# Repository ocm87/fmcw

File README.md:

# ELEC4907 FMCW/Dopper Radar Capstone Project
Year: 2024-2025

Supervisor: Shulabh Gupta

Team Members: Carter Livermore, Jin Her, Max Hecht, Owen MacIntosh

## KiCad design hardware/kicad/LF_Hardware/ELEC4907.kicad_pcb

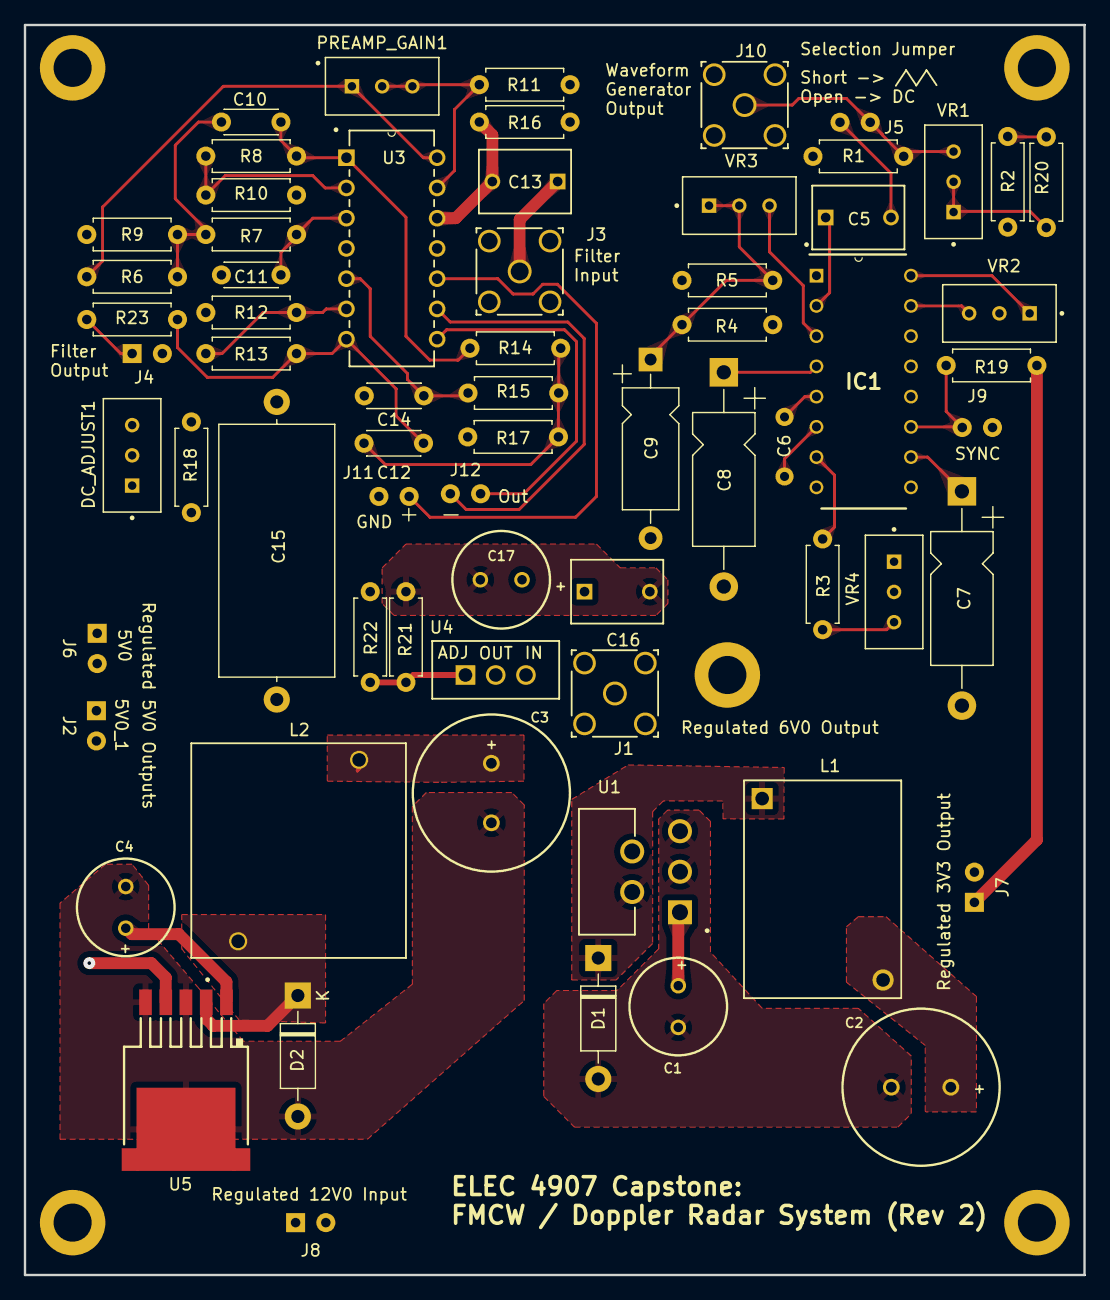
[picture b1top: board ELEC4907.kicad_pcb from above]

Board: 4 copper layers, 89.0 x 105.0 mm, 71 parts (0 on the bottom side), 40 nets.

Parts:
C1, C4, C17: 100uF; 100uF_RadialCap
C2, C3: 330uF; 330uF_radialCap
C5, C13, C16: 1uF; R82-D_KEM
C6: 0.47uF; 0.47uF_cap
C7, C8: 1uF; AxialCap_P18
C9: 10uF; Cap_P15
C10, C11, C12: 100pF; Disc_Cap_P5mm
C14: 150pF; Disc_Cap_P5mm
C15: 10uF; Axial_Cap_P25
D1, D2: 1N5819; D_DO-41_SOD81_P10.16mm_Horizontal
DC_ADJUST1: 100k; TRIM_3296W-1-503LF
GND: MountingHole_3.2mm_M3_ISO14580_Pad
GND#2, GND#3, GND#4: MountingHole_3.2mm_M3_ISO14580_Pad
IC1: XR2206CP-F; DIP794W56P254L2013H533Q16N
J1, J3, J10: RF2-04A-T-00-50-G; CONN_RF2-04A-T-00-50-G_ADM
J2, J4, J5, J6, J7, J8, J9, J11, J12: 2-54mm_Spacing
L1: IND_PE-526xx_V_PUL
L2: 330uH Inductor
PREAMP_GAIN1: 100k; TRIM_3296W-1-503LF
R1, R7: 100k; resistor
R2: 39k; resistor
R3: 33k; resistor
R4, R5: 4.7k; resistor
R6, R14: 82k; resistor
R8, R10, R12, R13: 27k; resistor
R9, R17: 1M; resistor
R11: 220; resistor
R15: 43k; resistor
R16, R19: 10k; resistor
R18: 5.6k; resistor
R20: 560k; resistor
R21: 1.5k; resistor
R22: 390; resistor
R23: 0; resistor
U1: LM2575T-3.3; (3v3)TO170P470X1016X2092-5P
U3: LT1214CN-PBF; PDIP-14_N_LIT
U4: LM317T; TO-220_STM
U5: LM2575S-5.0/NOPB; KTT0005B
VR1: 100k; TRIM_3296W-1-503LF
VR2, VR4: 25k; TRIM_3296W-1-503LF
VR3: 50k; TRIM_3296W-1-503LF

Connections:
/Filter/PRE_OUT: PREAMP_GAIN1.1, R6.1, U3.14 (OUT_D)
/Filter/STAGE1_OUT: C10.1, R8.2, R14.1, U3.1 (OUT_A)
/Filter/VREF: C11.1, C14.1, C15.1, DC_ADJUST1.2, DC_ADJUST1.3, R9.1, R10.1, R11.2, R12.1, R16.2, R17.1, R18.1
/Filter/Vcc: C1.1, C4.1, C8.1, C16.1, DC_ADJUST1.1, IC1.4 (VCC), J8.1, R4.1, U1.1 (VIN), U3.4 (V+), U4.3 (INPUT), U5.1 (VIN)
/Filter/VinLPF: C13.1, J3.1
/Filter/VoutLPF: C12.1, R13.2, R23.1, U3.7 (OUT_B)
/Power_Regulation/3V3: C2.1, J7.2, L1.2, R19.2, U1.4 (FB)
/Power_Regulation/3V3_UNREG: D1.1 (K), L1.1, U1.2 (OUTPUT)
/Power_Regulation/5V0: C3.1, J2.1, J6.2, L2.1, U5.4 (FB)
/Power_Regulation/5V0_UNREG: D2.1 (K), L2.2, U5.2 (OUT)
/Power_Regulation/6V0: C17.1, J1.1, R1.1, R22.2, U4.2 (OUTPUT)
/Waveform_Generator/Triangular_Waveform: J5.2, J10.1, R1.2, VR1.3
GND: C1.2, C2.2, C3.2, C4.2, C7.2, C8.2, C9.2, C15.2, C16.2, C17.2, D1.2 (A), D2.2 (A), GND.1, GND#2.1, GND#3.1, GND#4.1, IC1.1 (AMSI), IC1.12 (GND), J1.2 (GND), J1.3, J1.4, J1.5, J2.2, J3.2 (GND), J3.3, J3.4, J3.5, J4.1, J6.1, J7.1, J8.2, J9.2, J10.2 (GND), J10.3, J10.4, J10.5, J11.2, R2.2, R5.2, R18.2, R21.2, U1.3 (GND), U1.5 (ON/OFF), U3.11 (V-), U5.3 (GND), U5.5 (ON_OFF_N), U5.6 (PAD), VR2.2, VR4.1, VR4.2
unnamed: C9.1, R4.2, R5.1, VR3.1, VR3.2
unnamed: C10.2, R6.2, R7.1, R9.2
unnamed: C12.2, R14.2, R15.1, R17.2
unnamed: C7.1, IC1.10 (BIAS)
unnamed: IC1.3 (MO), VR3.3
unnamed: C5.1, IC1.2 (STO)
unnamed: IC1.15 (SYMA1), VR2.3
unnamed: IC1.16 (SYMA2), VR2.1
unnamed: IC1.11 (SYNCO), J9.1, R19.1
unnamed: C6.1, IC1.5 (TC1)
unnamed: C6.2, IC1.6 (TC2)
unnamed: IC1.7 (TR1), R3.1
unnamed: J4.2, R23.2
unnamed: C5.2, J5.1
unnamed: J11.1, U3.10 (IN_C+)
unnamed: J12.1, U3.8 (OUT_C)
unnamed: J12.2, U3.9 (IN_C-)
unnamed: R2.1, R20.2
unnamed: R3.2, VR4.3
unnamed: R20.1, VR1.1, VR1.2
unnamed: C11.2, R7.2, U3.3 (IN_A+)
unnamed: R8.1, R10.2, U3.2 (IN_A-)
unnamed: C14.2, R15.2, U3.5 (IN_B+)
unnamed: R12.2, R13.1, U3.6 (IN_B-)
unnamed: C13.2, R16.1, U3.12 (IN_D+)
unnamed: PREAMP_GAIN1.2, PREAMP_GAIN1.3, R11.1, U3.13 (IN_D-)
unnamed: R21.1, R22.1, U4.1 (ADJ)

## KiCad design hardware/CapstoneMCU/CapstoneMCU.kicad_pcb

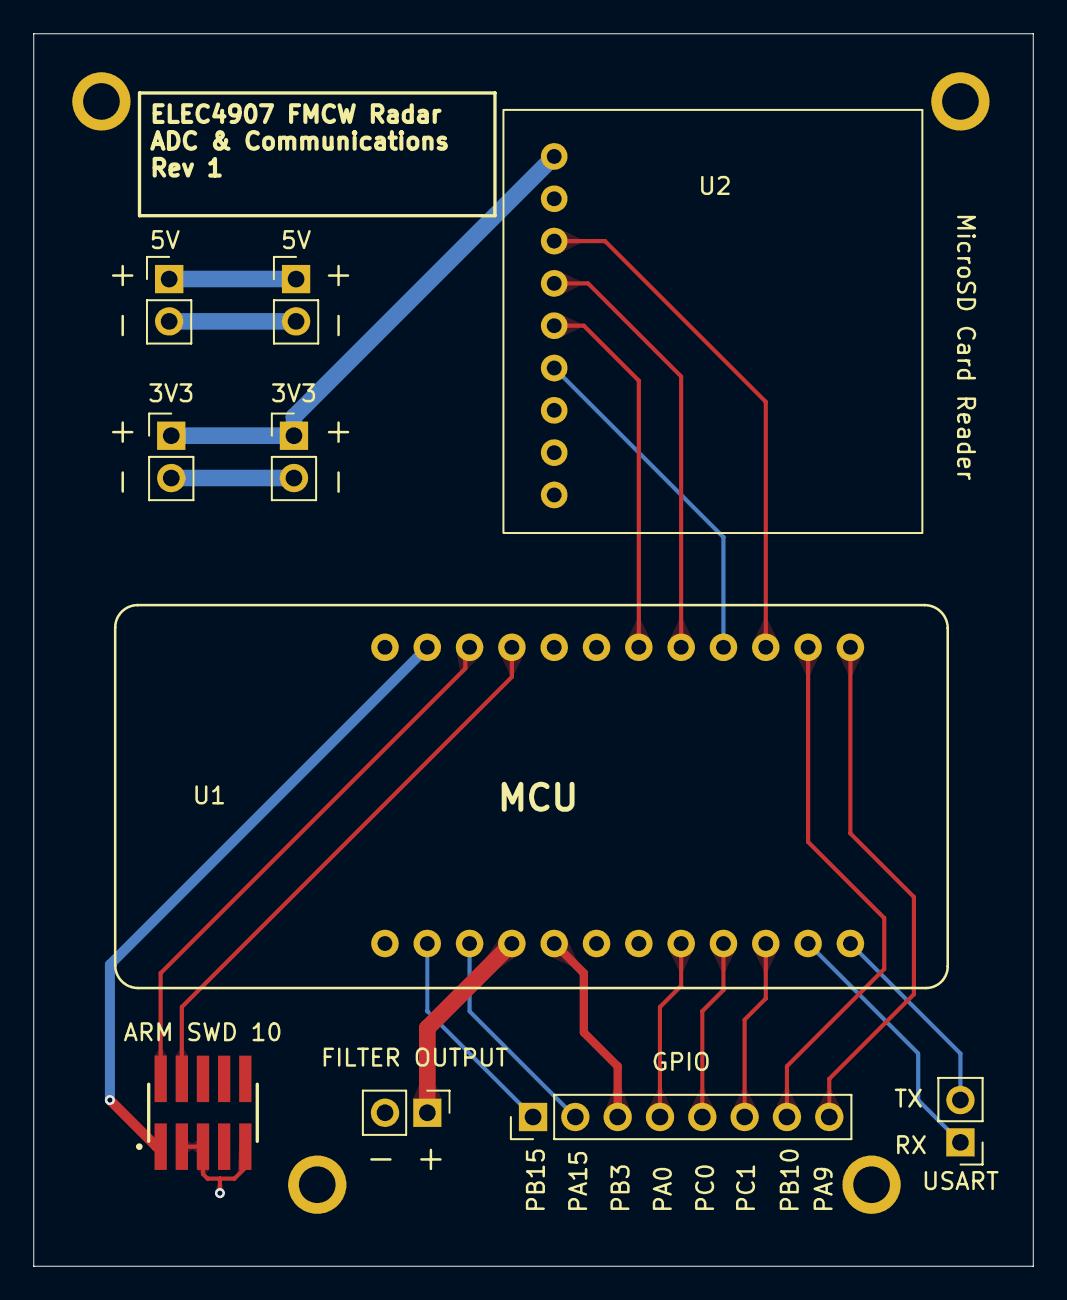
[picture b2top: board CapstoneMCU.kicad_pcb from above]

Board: 4 copper layers, 60.0 x 74.0 mm, 10 parts (0 on the bottom side), 21 nets.

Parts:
3V3: 3V3_MCU_JUMP; PinHeader_1x02_P2.54mm_Vertical
3V3#2: 3V3 Input; PinHeader_1x02_P2.54mm_Vertical
5V: 5V_MCU_JUMP; PinHeader_1x02_P2.54mm_Vertical
5V#2: 5V Input; PinHeader_1x02_P2.54mm_Vertical
ARM SWD 10: ARM_CORTEX_SWD_10; SAMTEC_FTSH-105-01-LM-DV-TR
FILTER OUTPUT: FILTER_OUTPUT; PinHeader_1x02_P2.54mm_Vertical
GPIO: GPIO_OUT; PinHeader_1x08_P2.54mm_Vertical
U1: SEEED_WIO_E5_MINI; Wio_e5
U2: microSD_Card_Breakout1; adafruit_sd_card_spi
USART: USART; PinHeader_1x02_P2.54mm_Vertical

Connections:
/3V3: 3V3.1, 3V3#2.1, U2.1 (3V)
/5V: 5V.1, 5V#2.1
/GND: 3V3.2, 3V3#2.2, 5V.2, 5V#2.2, ARM SWD 10.3 (GND), ARM SWD 10.5 (GND), ARM SWD 10.9 (GND_DET), FILTER OUTPUT.2, U1.1 (GND), U1.18 (GND), U2.2 (GND)
/MISO: U1.20 (MISO), U2.4 (SO)
/MOSI: U1.19 (MOSI), U2.5 (SI)
/NSS: U1.21 (NSS), U2.6 (CS)
/PA0: GPIO.4, U1.8 (PA0)
/PA9: GPIO.8, U1.24 (PA9)
/PA15/SDA: GPIO.2, U1.3 (PA15)
/PB3/A3: GPIO.3, U1.5 (PB3)
/PB4/A4: FILTER OUTPUT.1, U1.4 (A4)
/PB10: GPIO.7, U1.23 (PB10)
/PB15/SCL: GPIO.1, U1.2 (PB15)
/PC0: GPIO.5, U1.9 (PC0)
/PC1: GPIO.6, U1.10 (PC1)
/SCK: U1.22 (SCK), U2.3 (CLK)
/SWCLK: ARM SWD 10.4 (SWCLK), U1.16 (SWCLK)
/SWDIO: ARM SWD 10.2 (SWDIO), U1.15 (SWDIO)
/USART_RX: U1.11 (USART_RX), USART.1
/USART_TX: U1.12 (USART_TX), USART.2
/VCC_JTAG: ARM SWD 10.1 (VCC), U1.14 (3V3)

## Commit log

2025-04-05 added stm32 projects with basic programming instructions
2025-04-05 changed readme to markdown
2025-04-08 added post_processing folder
2025-04-09 added KiCad project and gerber files for MCU breakout pcb
2025-04-09 added LF folder
2025-04-09 Uploaded Post-Processing.
2025-04-09 Added LF Hardware KiCad Project
    This is the schematic and PCB for the LF hardware circuit.
2025-04-09 removed temp dir
2025-04-09 bom added
2025-04-09 updated filenames
2025-04-09 moved mcu symbols
2025-04-15 Added Fusion 360 Archive file for Chassis.
2025-04-16 Updated correct code for full chirp analysis.
